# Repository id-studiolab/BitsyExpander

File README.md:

[![CC BY 4.0][cc-by-shield]][cc-by]

# Bitsy Expander

An expansion board adding support for the Grove solderless connector system, a WiFi radio, and LiPo battery charging circuitry to Adafruit ItsyBitsy Development Boards.

Compatible with all ItsyBitsy boards, the Bitsy Expander is available in two distinct flavors. The silkscreens on each flavor are specifically tailored to either the [ItsyBitsy M4 Express](https://www.adafruit.com/product/3800) or the [ItsyBitsy RP2040](https://www.adafruit.com/product/4888).

**Jump ahead:**

* [Bitsy Expander M4](#bitsy-expander-m4)
* [Bitsy Expander RP2040](#bitsy-expander-rp2040)
* [General Information](#general-information)
* [FAQ](#faq)
* [Version History](#version-history)

## Bitsy Expander M4

### Preview

### Features

* 12 Grove Headers
  - 5 Digital Headers with overlapping (shingled) pins: D2, D3, D4, D7, D13
  - 1 Digital Header with exclusive pins: SERIAL1
  - 3 Analog Headers with exclusive pins: A0, A2, A4
  - 3 I²C Headers
* ESP32-WROOM Co-Processor for WiFi and BLE
* 1 JST SH 4-pin connector for Qwiic and STEMMA QT components (I²C)
* 1 JST PH 2-pin connector for 3.7V LiPo Batteries (chargeable via ItsyBitsy's USB port)
* 1 Logic-shifted output (allows driving components requiring 5V logic while powered via USB)

> NOTE: In shingled pin headers, each header's second pin is shared with the first pin in the header above it. Therefore, using one disables the other. For instance, using pins D3 and D4 in the  D3-labeled header disallows the use of D4 in the D4-labeled header.

### Pinout Diagrams

Additional resources and pinout diagrams are available **[here](M4_info.md)**.

## Bitsy Expander RP2040

### Preview

### Features

* 12 Grove Headers
  - 5 Digital Headers with overlapping (shingled) pins: D2, D3, D4, D7, D13
  - 1 Digital Header with exclusive pins: UART0
  - 3 Analog Headers with exclusive pins: A0, A2, A3 (A2 and A3 contain digital pins for their second pins)
  - 3 I²C Headers
* ESP32-WROOM Co-Processor for WiFi and BLE
* 1 JST SH 4-pin connector for Qwiic and STEMMA QT components (I²C)
* 1 JST PH 2-pin connector for 3.7V LiPo Batteries (chargeable via ItsyBitsy's USB port)
* 1 Logic-shifted output (allows driving components requiring 5V logic while powered via USB)

> NOTE: In shingled pin headers, each header's second pin is shared with the first pin in the header above it. Therefore, using one disables the other. For instance, using pins D3 and D4 in the  D3-labeled header disallows the use of D4 in the D4-labeled header.

### Pinout Diagrams

Additional resources and pinout diagrams are available **[here](RP2040_info.md)**.

## General Information

### WiFi and BLE

The Bitsy Expander uses an ESP32 WROOM module to provide WiFi functionality to the microcontroller using [Adafruit's fork](https://github.com/adafruit/nina-fw) of the Arduino NINA-W102 firmware. In CircuitPython, this library also allows for the use of Bluetooth Low Energy (BLE).

To use the module with Circuitpython, use the [esp32spi](https://docs.circuitpython.org/projects/esp32spi/en/latest/) library. For Arduino, [Adafruit's forked WiFiNINA](https://github.com/adafruit/WiFiNINA/) library is required.

The ESP32 module is connected as follows:

| ESP32 Pin        | ItsyBitsy Pin |
| ---------------- | ------------- |
| Chip Select (CS) | D9            |
| Busy (BSY)       | D11           |
| Reset (RST)      | D12           |
| SPI Clock (SCK)  | SCK           |
| SPI MISO         | MISO          |
| SPI MOSI         | MOSI          |

### Solder Jumpers

The underside of the Bitsy Expander features a number of solder jumpers:

#### WIFI PIN:

These pins are used to connect the ItsyBitsy board to the ESP32 module on the Expander. If WiFi functionality is not needed but additional digital pins are required, these jumpers can be used to disable the WiFi module and make additional pins available in the double-row header on the upper side of the board. The traces between the middle and left pads must be severed before soldering a jumper in place between the middle and the right pads to do so.

#### ESP32 CONFIG:

These solder jumpers are normally open. If the ESP32 module requires a firmware update, these jumpers may be used to enable the ItsyBitsy to serve as a programming interface for the ESP32 module. Refer to [Adafruit's excellent tutorial](https://learn.adafruit.com/upgrading-esp32-firmware) on flashing firmware onto the ESP32.

#### BATTERY CHARGING:

The default battery charging current is 100mA. A faster, 500mA charging mode is available for batteries that support it. It can be enabled by closing the solder jumper.

## FAQ

#### How do I recognize which Bitsy Expander I have?

The easiest way to identify which Bitsy Expander flavor you own is checking the label on the back of the board. **RP2040** or **M4** stated on the label indicates the flavor of your Expander. Older M4 Expanders have an **empty label** (and are also recognizable by the lack of an I²C header at the top). 

#### How do I recognize which ItsyBitsy Development Board I am using?

The **ItsyBitsy M4 Express** features **one (RESET) button**. (So do most other ItsyBitsy Development boards, so always verify with the silkscreen.)
The **ItsyBitsy RP2040** features **two (BOOT, RESET) buttons**.

#### Will any ItsyBitsy-type microcontroller work with any Bitsy Expander?

In principle, yes. The silkscreen on either flavor is specifically designed for either the [ItsyBitsy M4 Express](https://www.adafruit.com/product/3800) or the [ItsyBitsy RP2040](https://www.adafruit.com/product/4888), respectively. Pinouts differ only slightly between ItsyBitsy Development boards, however. The M4 Expander, for instance, has also been used successfully with the [ItsyBitsy M0 Express](https://www.adafruit.com/product/3727) in the past. This repository includes a number of pinout diagrams for different use-cases.

## Version History

| Version | Comment                                                      | Known Issues                                                 | Flavors            |
| ------- | ------------------------------------------------------------ | ------------------------------------------------------------ | ------------------ |
| **1.0** | Initial version                                              | Using pin D13 to drive the ESP Chip Select (CS) causes interference between the microcontroller's internal LED and the pull-up resistor | M4 Express         |
| 1.1     | – Uses pin D9 instead of D13 to drive the ESP Chip Select to prevent interference  <br />– Adds a test point to the expander's underside for VBAT accessibility | Only two Grove headers provide direct access to Analog pins of used with RP2040 | M4 Express, RP2040 |
| **2.0** | – Adds a top-edge JST SH 4-pin connector for Qwiic and STEMMA QT compatibility  <br />– Repositions pin A3 for better RP2040 analog pin access<br />– Adds "NC" (not connected) labels to double-row header pins that are not normally broken out | Tilde (~) marks inaccurately represent freely configurable PWM pins on RP2040. *Note: all pins support PWM, subject to certain limitations.* | RP2040             |
| 2.1     | Silkscreen update to accurately depict a selection of freely configurable PWM pins on RP2040, preventing configuration conflicts among them |                                                              | RP2040             |
| **3.0** | – Reinstates original pin layout (identical to V1) for sequential analog pin placement on M4 Express <br />– Maintains JST SH-4 connector and VBAT test point inherited from previous versions |                                                              | M4 Express         |

This is the sibling of the [Nano Expander](https://github.com/id-studiolab/NanoExpander), a Grove expansion board for [Arduino Nano 33 IoT](https://store.arduino.cc/products/arduino-nano-33-iot).

This work is licensed under a
[Creative Commons Attribution 4.0 International License][cc-by].

[![CC BY 4.0][cc-by-image]][cc-by]

[cc-by]: http://creativecommons.org/licenses/by/4.0/
[cc-by-image]: https://i.creativecommons.org/l/by/4.0/88x31.png
[cc-by-shield]: https://img.shields.io/badge/License-CC%20BY%204.0-lightgrey.svg

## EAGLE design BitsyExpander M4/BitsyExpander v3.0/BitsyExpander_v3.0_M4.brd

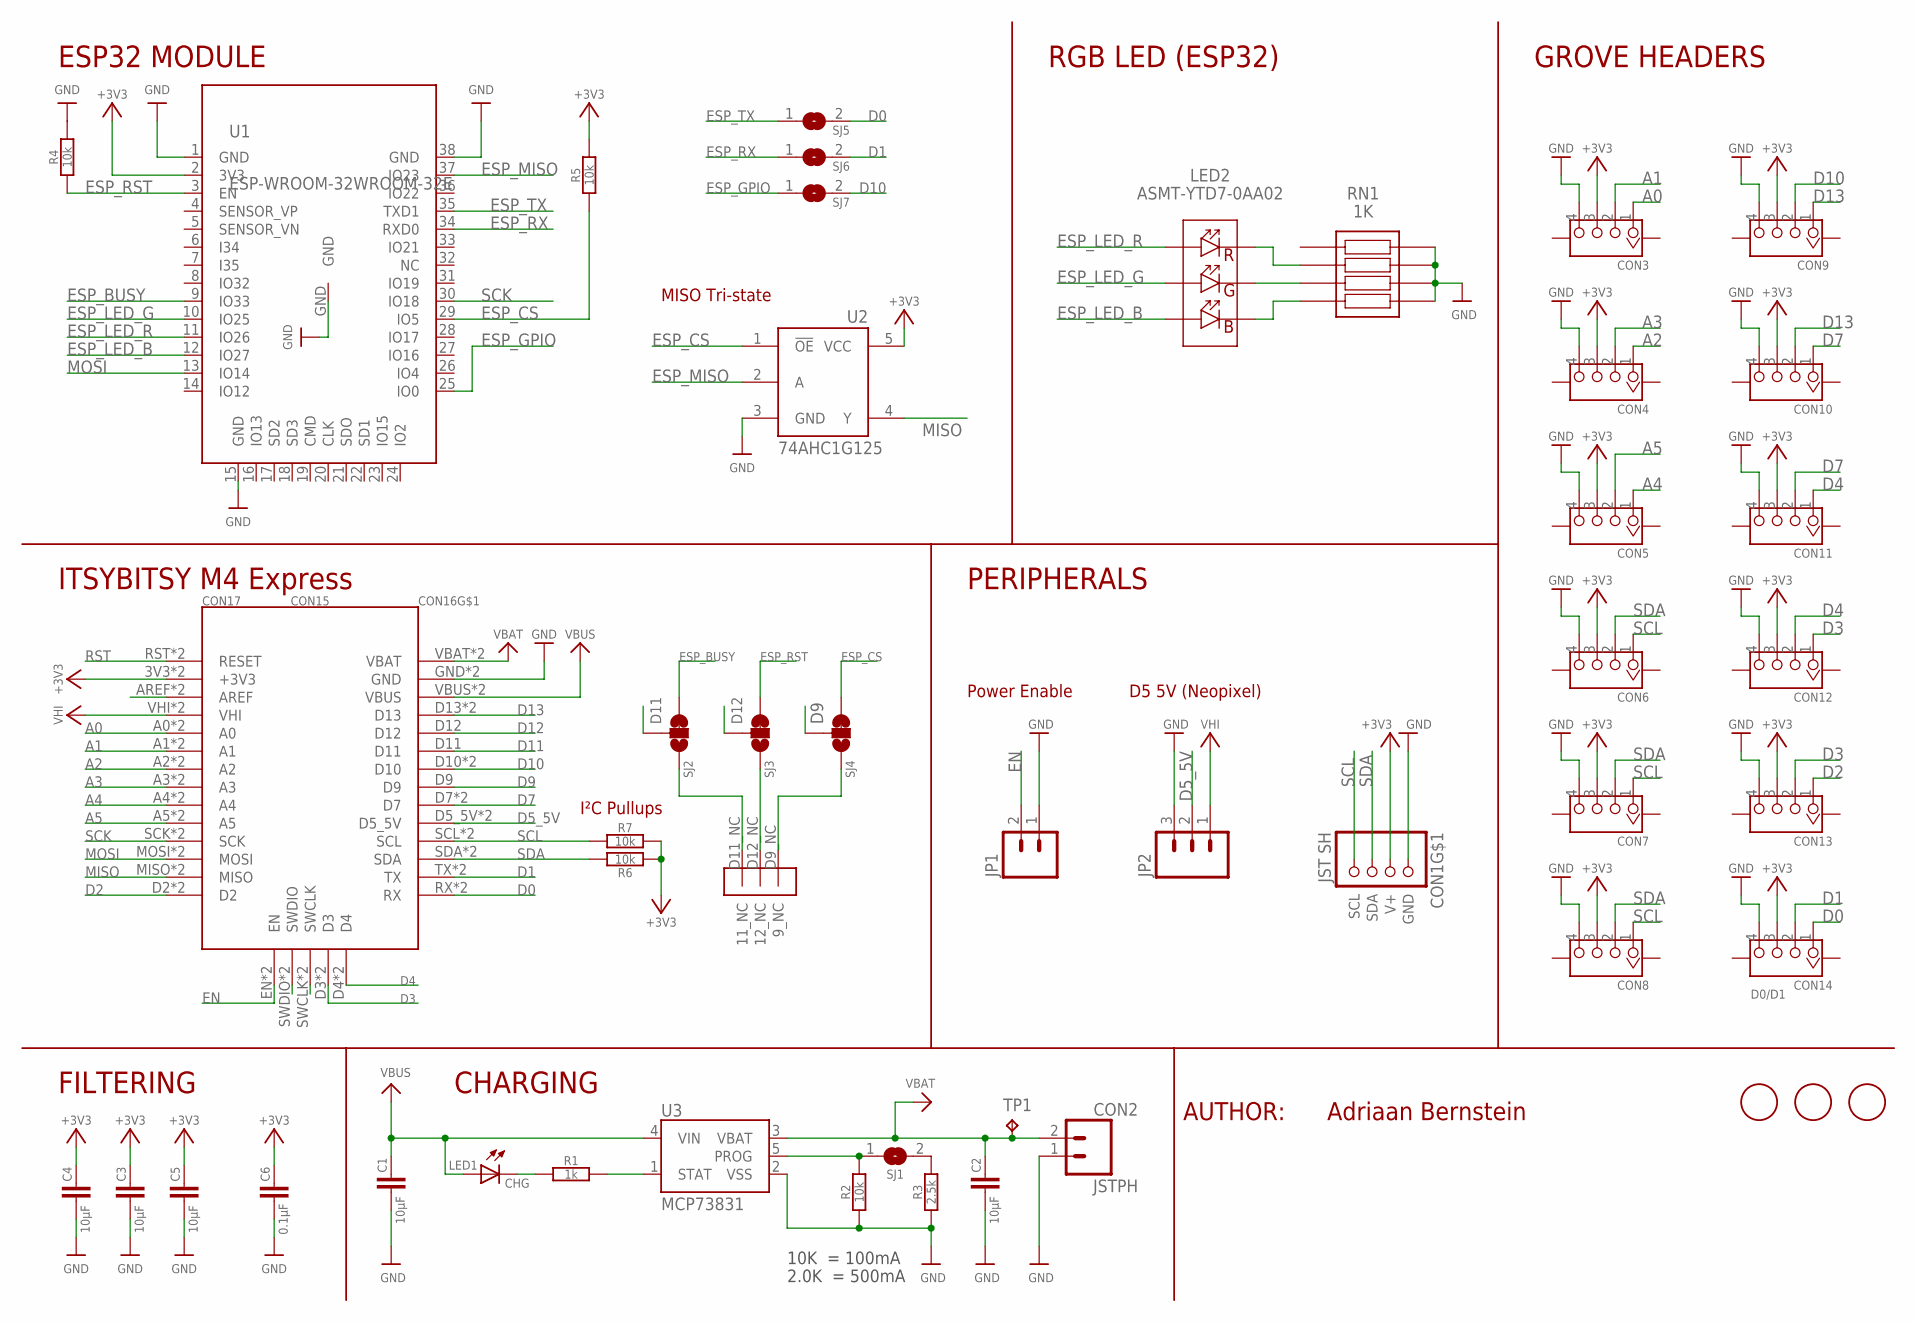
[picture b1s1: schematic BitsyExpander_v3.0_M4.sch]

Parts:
C1, C2, C3, C4, C5: 10µF; C0805
C6: 0.1µF; C0805
CON1: JST SH; JST_SH4
CON2: JSTPH; JST-2-SMD
CON3, CON4, CON5, CON6, CON7, CON8, CON9, CON10, CON11, CON12, CON13, CON14: H4P-SMD-2.0; HW4-PTH-2.0
CON15: ITSYBITSY_EDGE_DEBUG; ITSYBITSY_PTH_EDGE_DEBUG
CON16: ITSYBITSY_EDGE_GND; ITSYBITSY_SMD_EDGE_GND
CON17: ITSYBITSY_EDGE_PWR_M4EXPRESS; ITSYBITSY_SMD_EDGE_PWR_M4EXPRESS
FD1, FD2, FD3: FIDUCIAL; FIDUCIAL_1MM
JP1: M02PTH; 1X02
JP2: M03PTH; 1X03
LED1: CHG; CHIP-LED0603
LED2: ASMT-YTD7-0AA02; ASMTYTD70AA02
R1: 1k; R0603
R2, R4, R5, R6, R7: 10k; R0603
R3: 2.5k; R0603
RN1: 1K; CAY1647R0F4LF
SJ1, SJ5, SJ6, SJ7: SJ
SJ_D11: SJ2; SJ_2WAY_CLOSED
SJ_D12: SJ3; SJ_2WAY_CLOSED
SJ_D13: SJ4; SJ_2WAY_CLOSED
TP1: TPB1,27; B1,27
U1: ESP-WROOM-32WROOM-32E; ESP-WROOM-32E
U2: 74AHC1G125; SOT23-5L
U3: MCP73831; SOT23-5

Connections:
2.5K: R3.2, SJ1.2
10K: R2.2, SJ1.1, U3.5 (PROG)
+3V3: C3.1, C4.1, C5.1, C6.1, CON1.2 (V+), CON3.3, CON4.3, CON5.3, CON6.3, CON7.3, CON8.3, CON9.3, CON10.3, CON11.3, CON12.3, CON13.3, CON14.3, CON17.3V3 (+3V3), CON17.3V3_2 (+3V3), R5.2, R6.1, R7.1, U1.2 (3V3), U2.5 (VCC)
+5V: CON17.VHI, CON17.VHI_2 (VHI), JP2.1
A0: CON3.1, CON17.A0, CON17.A0_2 (A0)
A1: CON3.2, CON17.A1, CON17.A1_2 (A1)
A2: CON4.1, CON17.A2, CON17.A2_2 (A2)
A3: CON4.2, CON17.A3, CON17.A3_2 (A3)
A4: CON5.1, CON17.A4, CON17.A4_2 (A4)
A5: CON5.2, CON17.A5, CON17.A5_2 (A5)
AREF: CON17.AREF, CON17.AREF_2 (AREF)
CHG: LED1.C, R1.1
D0: CON14.1, CON15.RX, CON15.RX_2 (RX), SJ5.2
D1: CON14.2, CON16.TX, CON16.TX_2 (TX), SJ6.2
D2: CON13.1, CON15.D2, CON15.D2_2 (D2)
D3: CON12.1, CON13.2, CON15.D3, CON15.D3_2 (D3)
D4: CON11.1, CON12.2, CON15.D4, CON15.D4_2 (D4)
D5_5V: CON16.D5_5V, CON16.D5_5V_2 (D5_5V), JP2.2
D7: CON10.1, CON11.2, CON16.D7, CON16.D7_2 (D7)
D9: CON16.D9, SJ_D13.2
D9_NC: CON16.D9_NC (9_NC), SJ_D13.3
D10: CON9.2, CON16.D10, CON16.D10_2 (D10), SJ7.2
D11: CON16.D11, SJ_D11.2
D11_NC: CON16.D11_NC (11_NC), SJ_D11.3
D12: CON16.D12, SJ_D12.2
D12_NC: CON16.D12_NC (12_NC), SJ_D12.3
D13: CON9.1, CON10.2, CON16.D13, CON16.D13_2 (D13)
EN: CON15.EN, CON15.EN_2 (EN), JP1.2
ESP_BUSY: SJ_D11.1, U1.9 (IO33)
ESP_CS: R5.1, SJ_D13.1, U1.29 (IO5), U2.1 (!OE)
ESP_GPIO: SJ7.1, U1.25 (IO0)
ESP_LED_B: LED2.6 (A_BLUE), U1.12 (IO27)
ESP_LED_G: LED2.5 (A_GREEN), U1.10 (IO25)
ESP_LED_R: LED2.4 (A_RED), U1.11 (IO26)
ESP_MISO: U1.37 (IO23), U2.2 (A)
ESP_RST: R4.1, SJ_D12.1, U1.3 (EN)
ESP_RX: SJ6.1, U1.34 (RXD0)
ESP_TX: SJ5.1, U1.35 (TXD1)
GND: C1.2, C2.2, C3.2, C4.2, C5.2, C6.2, CON1.1 (GND), CON2.1, CON3.4, CON4.4, CON5.4, CON6.4, CON7.4, CON8.4, CON9.4, CON10.4, CON11.4, CON12.4, CON13.4, CON14.4, CON16.GND, CON16.GND_2 (GND), JP1.1, JP2.3, R2.1, R3.1, R4.2, RN1.5 (R4_2), RN1.6 (R3_2), RN1.7 (R2_2), RN1.8 (R1_2), U1.1 (GND), U1.15 (GND), U1.38 (GND), U1.GND, U2.3 (GND), U3.2 (VSS)
MISO: CON17.MISO, CON17.MISO_2 (MISO), U2.4 (Y)
MOSI: CON17.MOSI, CON17.MOSI_2 (MOSI), U1.13 (IO14)
unnamed: LED2.2 (K_GREEN), RN1.3 (R3_1)
unnamed: LED2.1 (K_BLUE), RN1.4 (R4_1)
unnamed: LED2.3 (K_RED), RN1.2 (R2_1)
unnamed: CON15.SWDIO, CON15.SWDIO_2 (SWDIO)
unnamed: CON15.SWCLK, CON15.SWCLK_2 (SWCLK)
RST: CON17.RST (RESET), CON17.RST_2 (RESET)
SCK: CON17.SCK, CON17.SCK_2 (SCK), U1.30 (IO18)
SCL: CON1.4 (SCL), CON6.1, CON7.1, CON8.1, CON16.SCL, CON16.SCL_2 (SCL), R7.2
SDA: CON1.3 (SDA), CON6.2, CON7.2, CON8.2, CON16.SDA, CON16.SDA_2 (SDA), R6.2
STAT: R1.2, U3.1 (STAT)
VBAT: C2.1, CON2.2, CON16.VBAT, CON16.VBAT_2 (VBAT), TP1.TP, U3.3 (VBAT)
VBUS: C1.1, CON16.VBUS, CON16.VBUS_2 (VBUS), LED1.A, U3.4 (VIN)

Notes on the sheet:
10K = 100mA
2.0K = 500mA
D0/D1
FILTERING
CHARGING
PERIPHERALS
GROVE HEADERS
ITSYBITSY M4 Express
ESP32 MODULE
RGB LED (ESP32)
MISO Tri-state
Power Enable
D5 5V (Neopixel)
I²C Pullups
AUTHOR:
Adriaan Bernstein

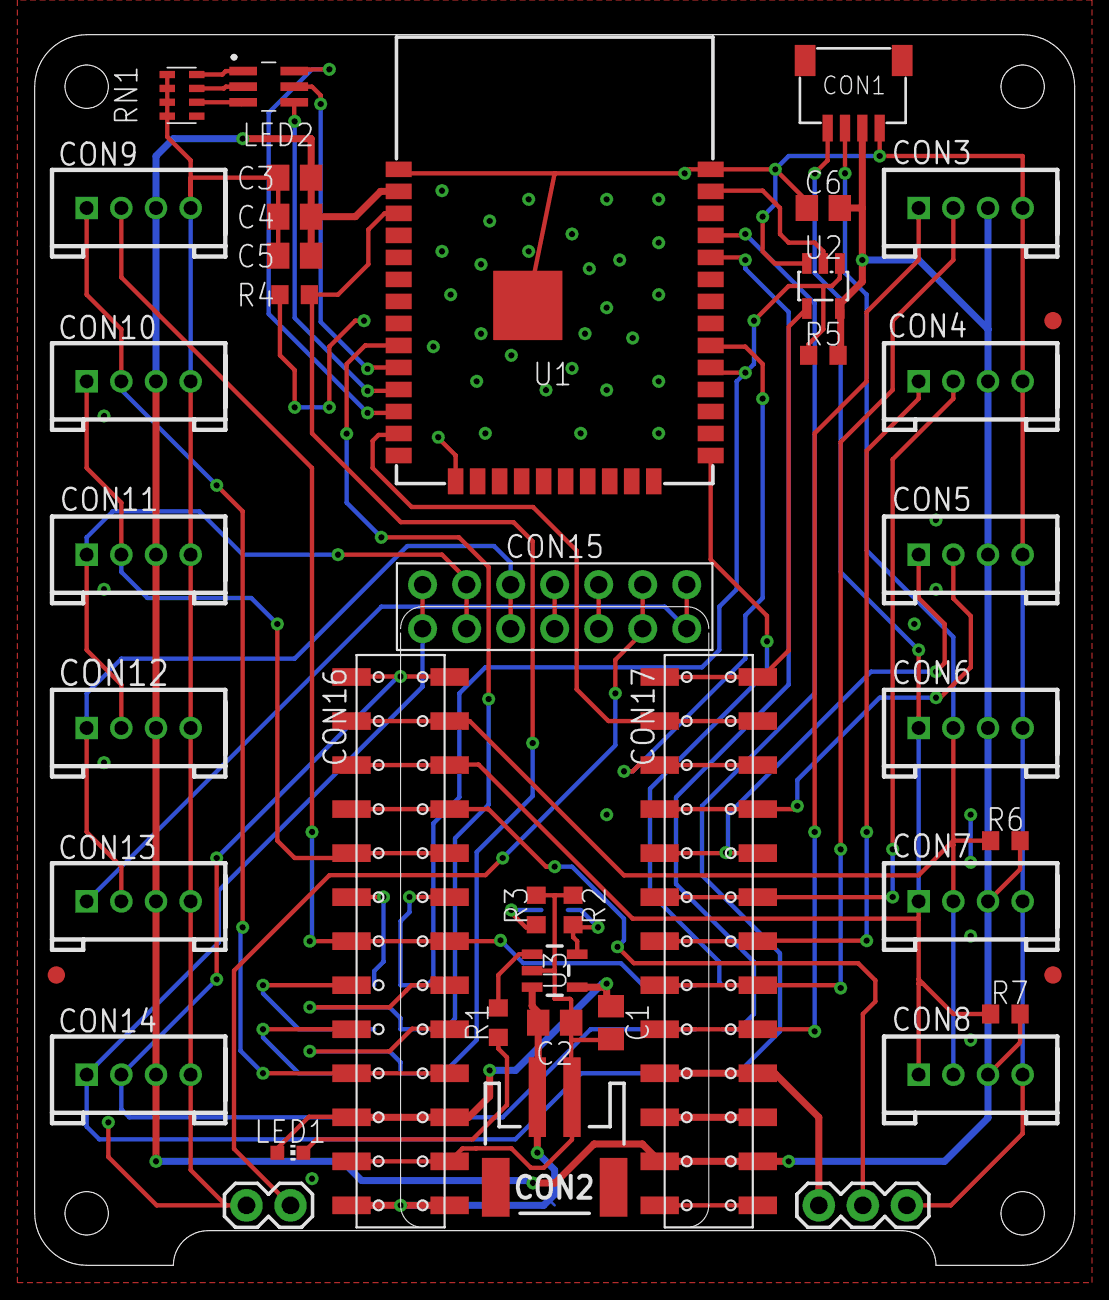
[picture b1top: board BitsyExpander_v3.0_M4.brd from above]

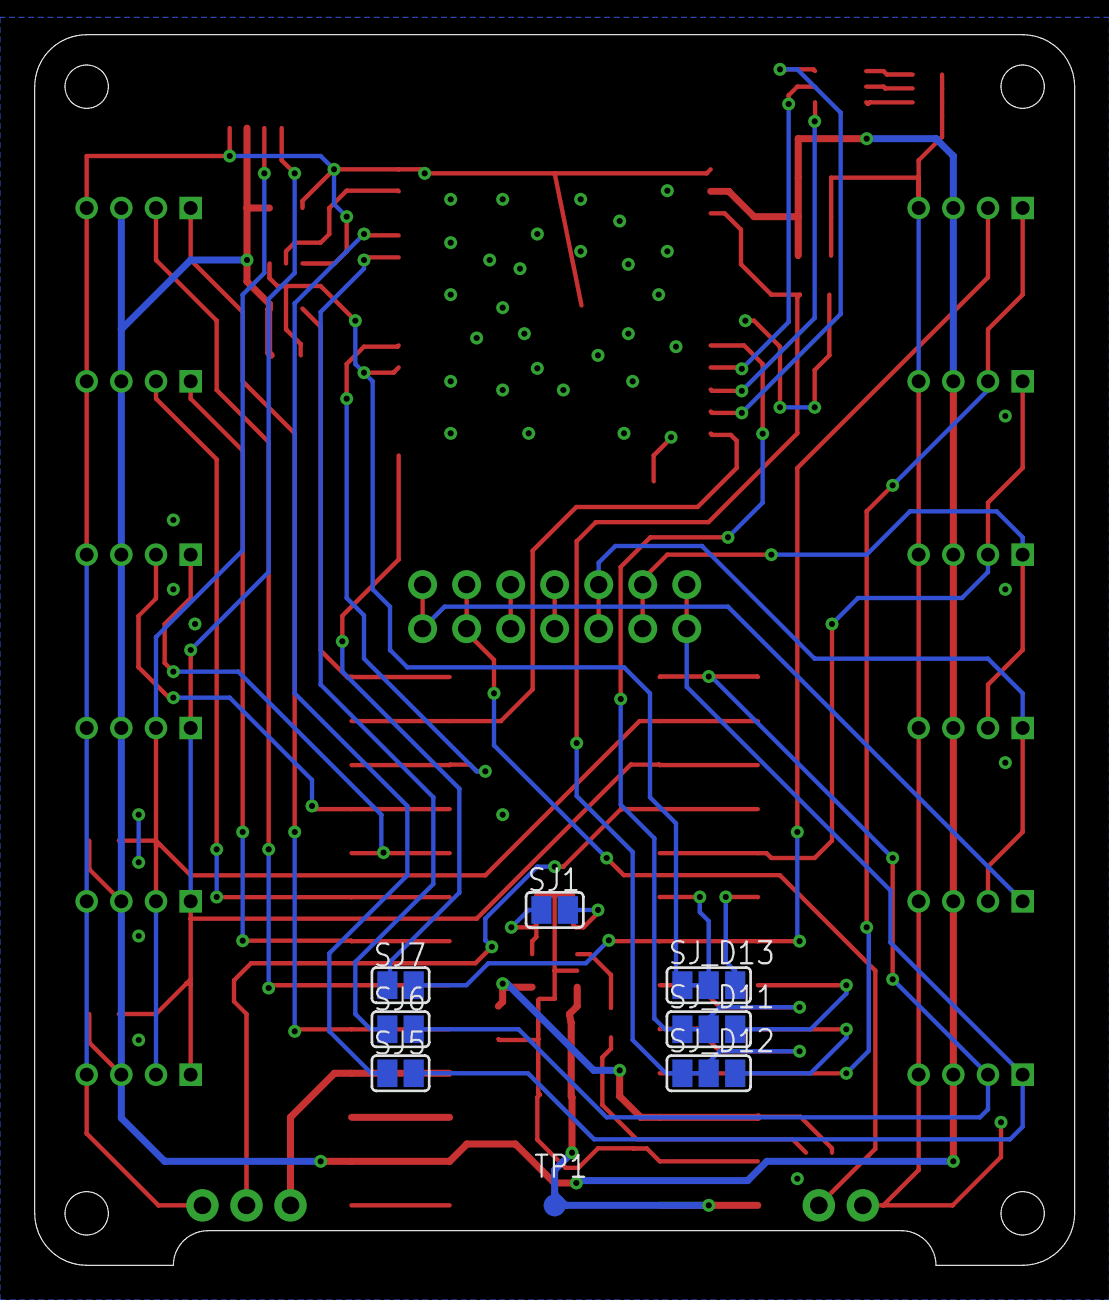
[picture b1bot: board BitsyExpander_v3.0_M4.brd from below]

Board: 2 copper layers, 60.0 x 71.0 mm, 49 parts (8 on the bottom side), 53 nets.

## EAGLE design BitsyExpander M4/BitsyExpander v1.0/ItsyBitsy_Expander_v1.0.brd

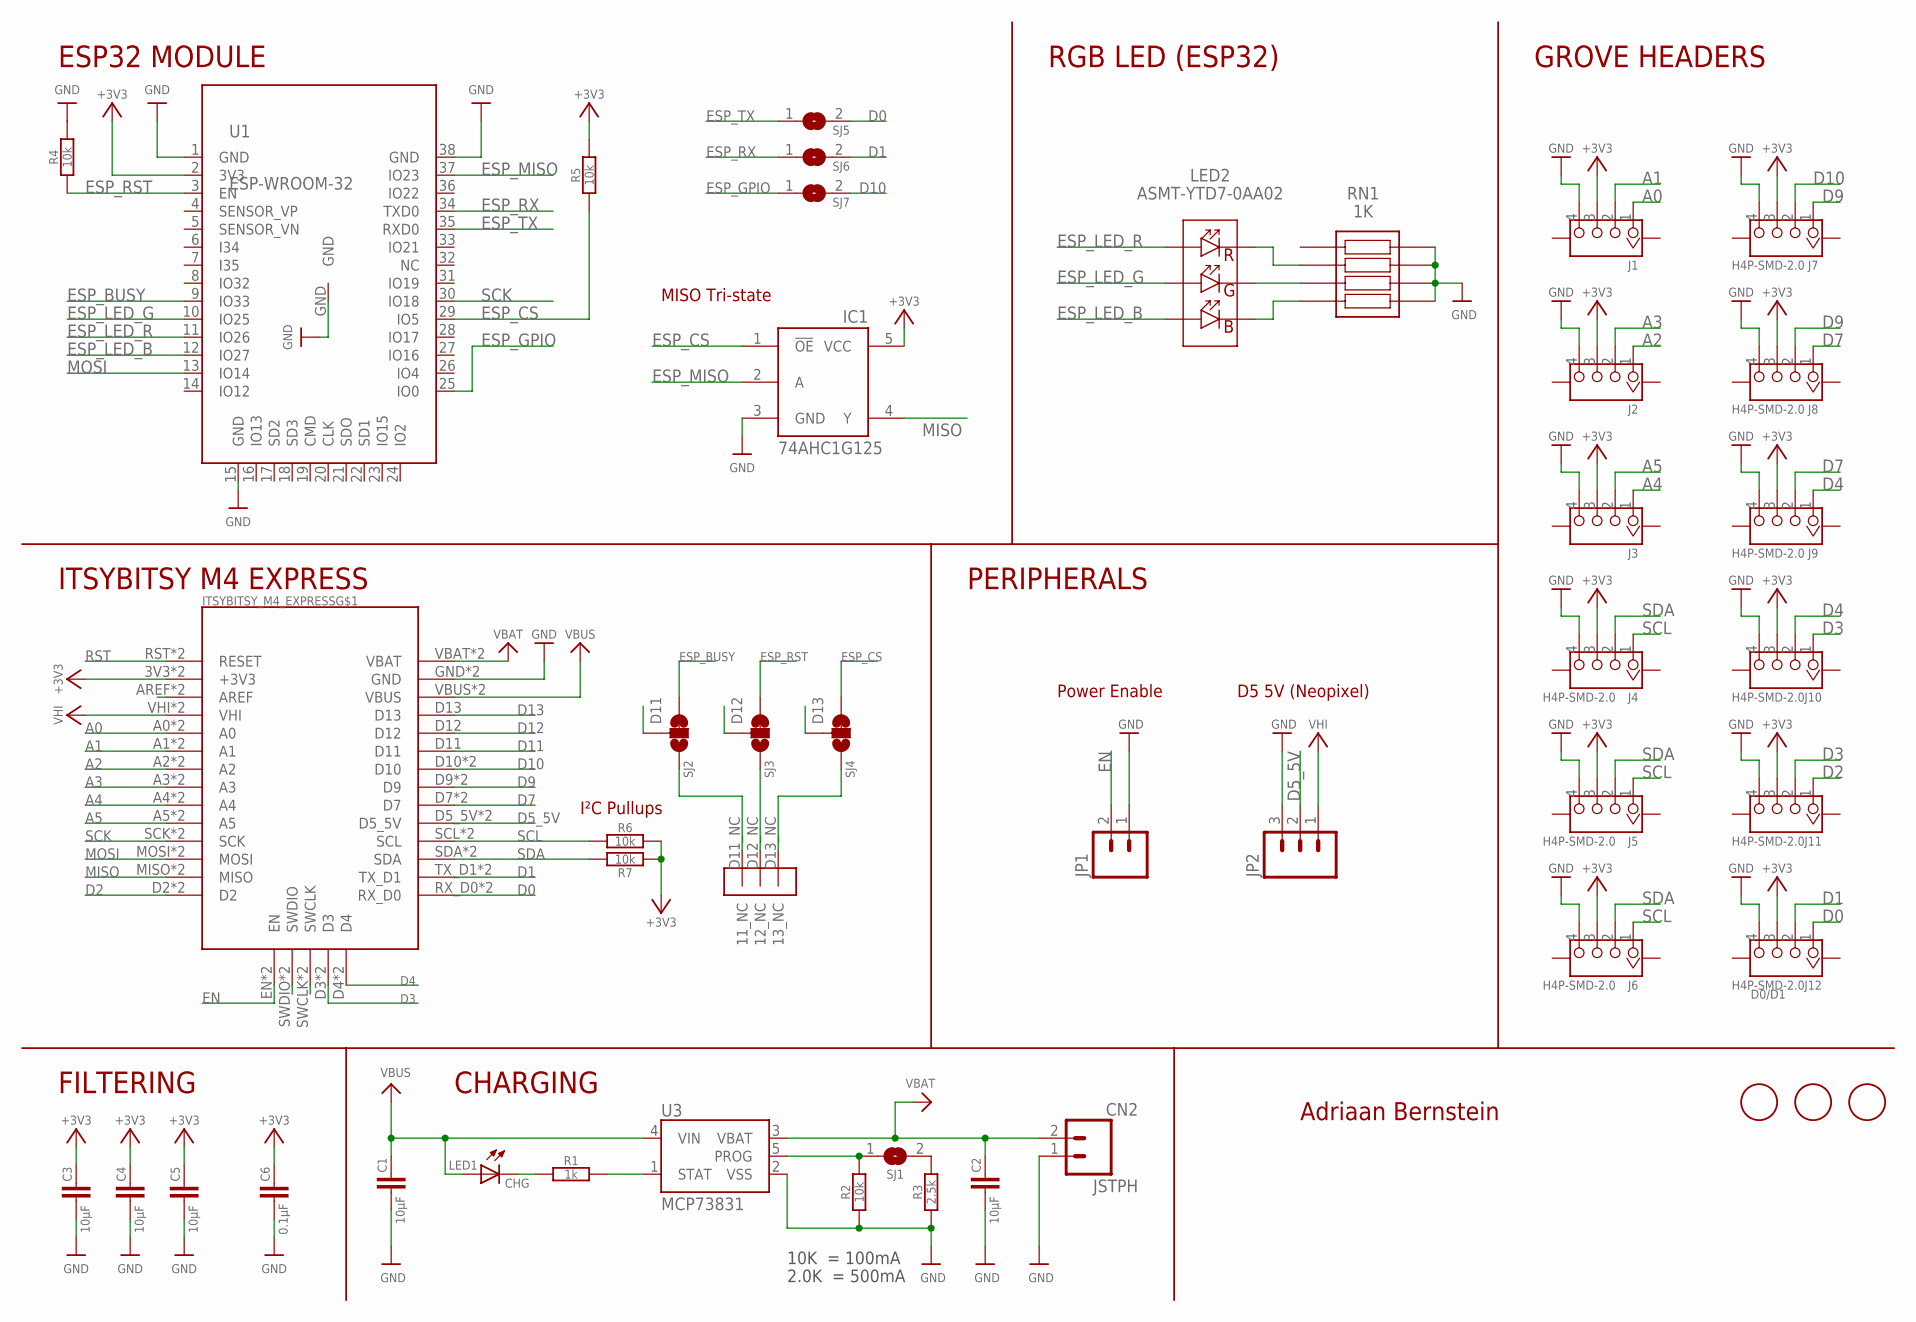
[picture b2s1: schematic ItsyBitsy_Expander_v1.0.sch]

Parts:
C1, C2, C3, C4, C5: 10µF; C0805
C6: 0.1µF; C0603
CN2: JSTPH; JST-2-SMD
IC1: 74AHC1G125; SOT23-5L
ITSYBITSY_M4_EXPRESS: ITSYBITSY_M4_NC; ITSYBITSY_M4_MIXED_DOUBLEHEADERS_ALL_NC
J1, J2, J3, J4, J5, J6, J7, J8, J9, J10, J11, J12: H4P-SMD-2.0; HW4-SMD-2.0
JP1: M02PTH; 1X02
JP2: M03PTH; 1X03
LED1: CHG; CHIP-LED0603
LED2: ASMT-YTD7-0AA02; ASMTYTD70AA02
R1: 1k; R0603
R2, R4, R5, R6, R7: 10k; R0603
R3: 2.5k; R0603
RN1: 1K; CAY1647R0F4LF
SJ1, SJ5, SJ6, SJ7: SJ
SJ_D11: SJ2; SJ_2WAY_CLOSED
SJ_D12: SJ3; SJ_2WAY_CLOSED
SJ_D13: SJ4; SJ_2WAY_CLOSED
U1: ESP-WROOM-32
U3: MCP73831; SOT23-5
U$23, U$35, U$36: FIDUCIAL; FIDUCIAL_1MM

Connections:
2.5K: R3.2, SJ1.2
10K: R2.2, SJ1.1, U3.5 (PROG)
+3V3: C3.1, C4.1, C5.1, C6.1, IC1.5 (VCC), ITSYBITSY_M4_EXPRESS.3V3 (+3V3), ITSYBITSY_M4_EXPRESS.3V3_2 (+3V3), J1.3, J2.3, J3.3, J4.3, J5.3, J6.3, J7.3, J8.3, J9.3, J10.3, J11.3, J12.3, R5.2, R6.1, R7.1, U1.2 (3V3)
+5V: ITSYBITSY_M4_EXPRESS.VHI, ITSYBITSY_M4_EXPRESS.VHI_2 (VHI), JP2.1
A0: ITSYBITSY_M4_EXPRESS.A0, ITSYBITSY_M4_EXPRESS.A0_2 (A0), J1.1
A1: ITSYBITSY_M4_EXPRESS.A1, ITSYBITSY_M4_EXPRESS.A1_2 (A1), J1.2
A2: ITSYBITSY_M4_EXPRESS.A2, ITSYBITSY_M4_EXPRESS.A2_2 (A2), J2.1
A3: ITSYBITSY_M4_EXPRESS.A3, ITSYBITSY_M4_EXPRESS.A3_3 (A3), J2.2
A4: ITSYBITSY_M4_EXPRESS.A4, ITSYBITSY_M4_EXPRESS.A4_2 (A4), J3.1
A5: ITSYBITSY_M4_EXPRESS.A5, ITSYBITSY_M4_EXPRESS.A5_2 (A5), J3.2
CHG: LED1.C, R1.1
D0: ITSYBITSY_M4_EXPRESS.RX_D0, ITSYBITSY_M4_EXPRESS.RX_D0_2 (RX_D0), J12.1, SJ5.2
D1: ITSYBITSY_M4_EXPRESS.TX_D1, ITSYBITSY_M4_EXPRESS.TX_D1_2 (TX_D1), J12.2, SJ6.2
D2: ITSYBITSY_M4_EXPRESS.D2, ITSYBITSY_M4_EXPRESS.D2_2 (D2), J11.1
D3: ITSYBITSY_M4_EXPRESS.D3, ITSYBITSY_M4_EXPRESS.D3_2 (D3), J10.1, J11.2
D4: ITSYBITSY_M4_EXPRESS.D4, ITSYBITSY_M4_EXPRESS.D4_2 (D4), J9.1, J10.2
D5_5V: ITSYBITSY_M4_EXPRESS.D5_5V, ITSYBITSY_M4_EXPRESS.D5_5V_2 (D5_5V), JP2.2
D7: ITSYBITSY_M4_EXPRESS.D7, ITSYBITSY_M4_EXPRESS.D7_2 (D7), J8.1, J9.2
D9: ITSYBITSY_M4_EXPRESS.D9, ITSYBITSY_M4_EXPRESS.D9_2 (D9), J7.1, J8.2
D10: ITSYBITSY_M4_EXPRESS.D10, ITSYBITSY_M4_EXPRESS.D10_2 (D10), J7.2, SJ7.2
D11: ITSYBITSY_M4_EXPRESS.D11, SJ_D11.2
D11_NC: ITSYBITSY_M4_EXPRESS.D11_NC (11_NC), SJ_D11.3
D12: ITSYBITSY_M4_EXPRESS.D12, SJ_D12.2
D12_NC: ITSYBITSY_M4_EXPRESS.D12_NC (12_NC), SJ_D12.3
D13: ITSYBITSY_M4_EXPRESS.D13, SJ_D13.2
D13_NC: ITSYBITSY_M4_EXPRESS.D13_NC (13_NC), SJ_D13.3
EN: ITSYBITSY_M4_EXPRESS.EN, ITSYBITSY_M4_EXPRESS.EN_2 (EN), JP1.2
ESP_BUSY: SJ_D11.1, U1.9 (IO33)
ESP_CS: IC1.1 (!OE), R5.1, SJ_D13.1, U1.29 (IO5)
ESP_GPIO: SJ7.1, U1.25 (IO0)
ESP_LED_B: LED2.6 (A_BLUE), U1.12 (IO27)
ESP_LED_G: LED2.5 (A_GREEN), U1.10 (IO25)
ESP_LED_R: LED2.4 (A_RED), U1.11 (IO26)
ESP_MISO: IC1.2 (A), U1.37 (IO23)
ESP_RST: R4.1, SJ_D12.1, U1.3 (EN)
ESP_RX: SJ6.1, U1.34 (TXD0)
ESP_TX: SJ5.1, U1.35 (RXD0)
GND: C1.2, C2.2, C3.2, C4.2, C5.2, C6.2, CN2.1, IC1.3 (GND), ITSYBITSY_M4_EXPRESS.GND, ITSYBITSY_M4_EXPRESS.GND_2 (GND), J1.4, J2.4, J3.4, J4.4, J5.4, J6.4, J7.4, J8.4, J9.4, J10.4, J11.4, J12.4, JP1.1, JP2.3, R2.1, R3.1, R4.2, RN1.5 (R4_2), RN1.6 (R3_2), RN1.7 (R2_2), RN1.8 (R1_2), U1.1 (GND), U1.15 (GND), U1.38 (GND), U1.GND, U3.2 (VSS)
MISO: IC1.4 (Y), ITSYBITSY_M4_EXPRESS.MISO, ITSYBITSY_M4_EXPRESS.MISO_2 (MISO)
MOSI: ITSYBITSY_M4_EXPRESS.MOSI, ITSYBITSY_M4_EXPRESS.MOSI_2 (MOSI), U1.13 (IO14)
unnamed: LED2.2 (K_GREEN), RN1.3 (R3_1)
unnamed: LED2.1 (K_BLUE), RN1.4 (R4_1)
unnamed: LED2.3 (K_RED), RN1.2 (R2_1)
unnamed: ITSYBITSY_M4_EXPRESS.AREF, ITSYBITSY_M4_EXPRESS.AREF_2 (AREF)
unnamed: ITSYBITSY_M4_EXPRESS.SWDIO, ITSYBITSY_M4_EXPRESS.SWDIO_2 (SWDIO)
unnamed: ITSYBITSY_M4_EXPRESS.SWCLK, ITSYBITSY_M4_EXPRESS.SWCLK_2 (SWCLK)
RST: ITSYBITSY_M4_EXPRESS.RST (RESET), ITSYBITSY_M4_EXPRESS.RST_2 (RESET)
SCK: ITSYBITSY_M4_EXPRESS.SCK, ITSYBITSY_M4_EXPRESS.SCK_2 (SCK), U1.30 (IO18)
SCL: ITSYBITSY_M4_EXPRESS.SCL, ITSYBITSY_M4_EXPRESS.SCL_2 (SCL), J4.1, J5.1, J6.1, R6.2
SDA: ITSYBITSY_M4_EXPRESS.SDA, ITSYBITSY_M4_EXPRESS.SDA_2 (SDA), J4.2, J5.2, J6.2, R7.2
STAT: R1.2, U3.1 (STAT)
VBAT: C2.1, CN2.2, ITSYBITSY_M4_EXPRESS.VBAT, ITSYBITSY_M4_EXPRESS.VBAT_2 (VBAT), U3.3 (VBAT)
VBUS: C1.1, ITSYBITSY_M4_EXPRESS.VBUS, ITSYBITSY_M4_EXPRESS.VBUS_2 (VBUS), LED1.A, U3.4 (VIN)

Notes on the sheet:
10K = 100mA
2.0K = 500mA
D0/D1
FILTERING
CHARGING
PERIPHERALS
GROVE HEADERS
ITSYBITSY M4 EXPRESS
ESP32 MODULE
RGB LED (ESP32)
MISO Tri-state
Power Enable
D5 5V (Neopixel)
Adriaan Bernstein
I²C Pullups

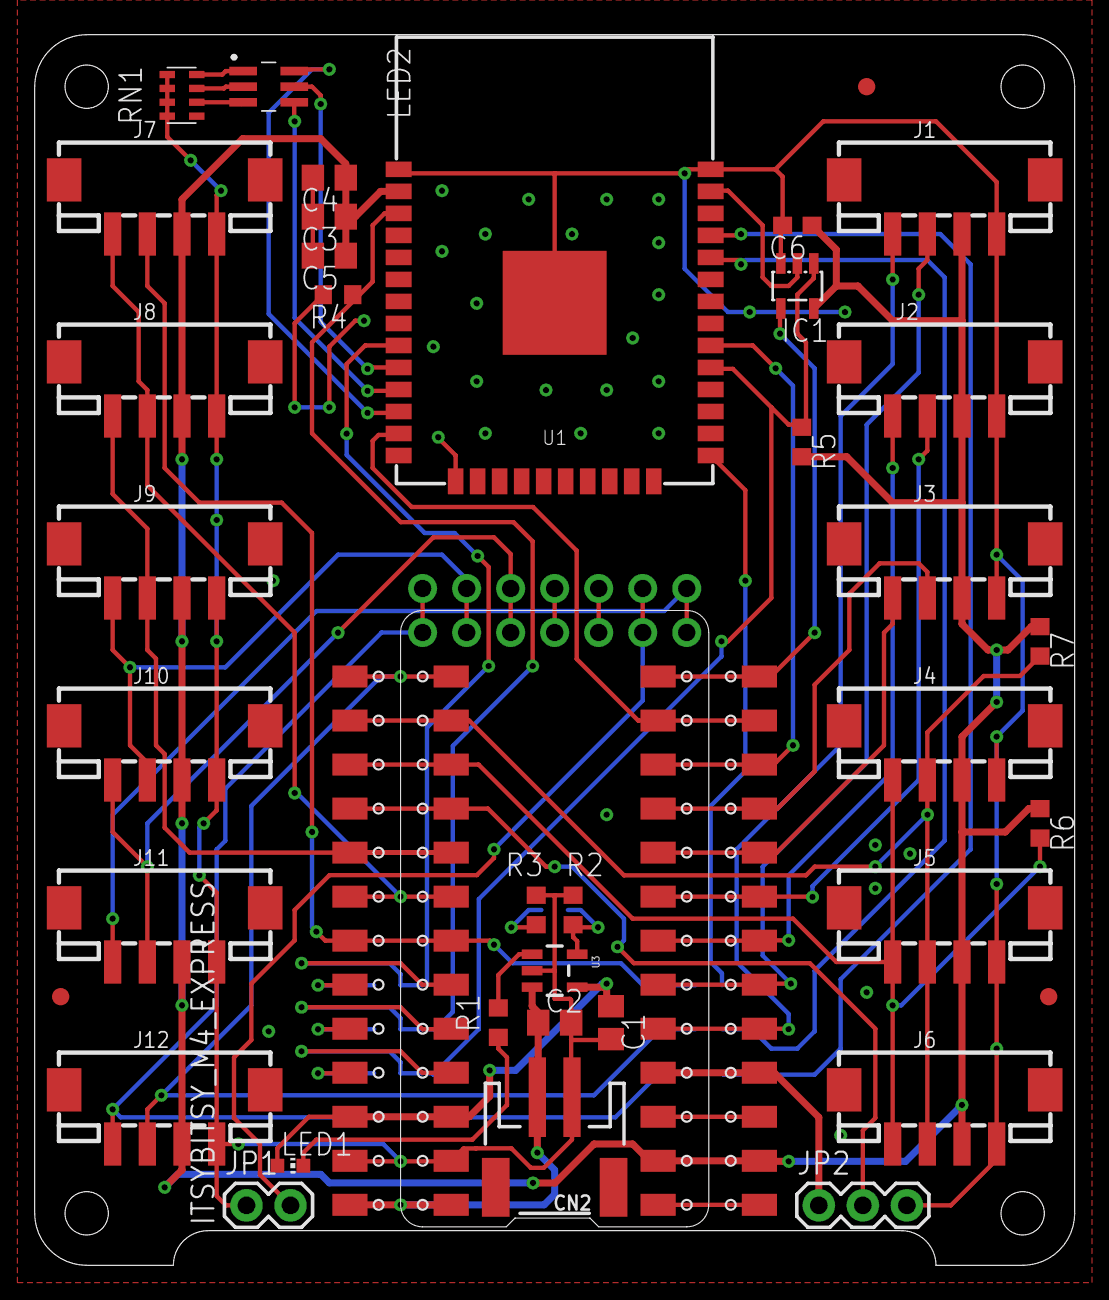
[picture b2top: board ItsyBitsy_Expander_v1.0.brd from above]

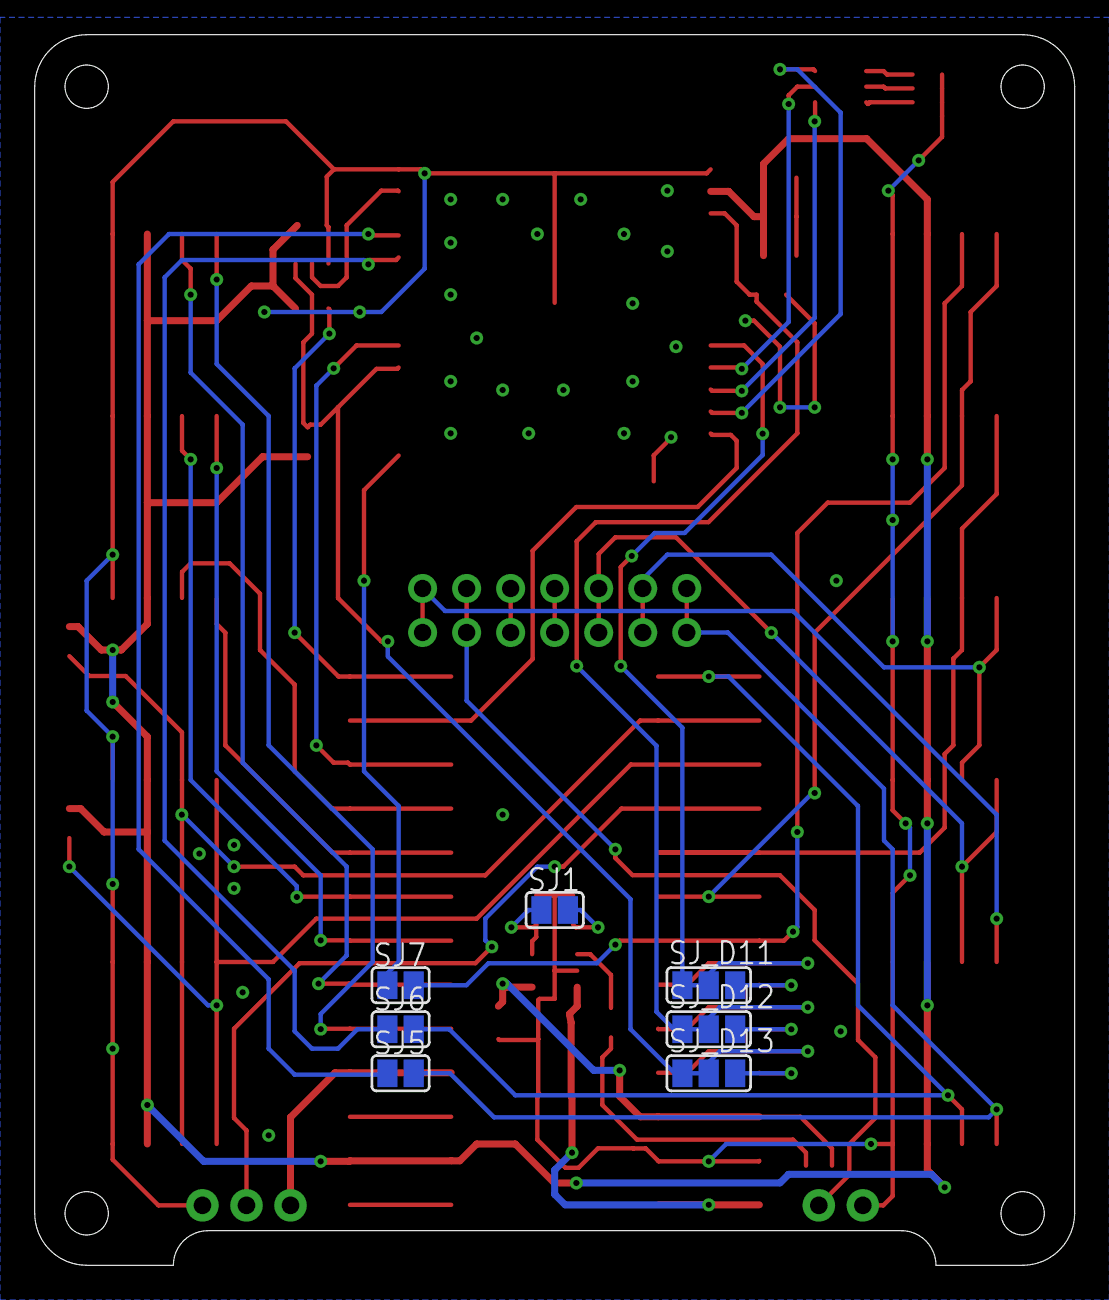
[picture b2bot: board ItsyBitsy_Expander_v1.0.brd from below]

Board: 2 copper layers, 60.0 x 71.0 mm, 45 parts (7 on the bottom side), 53 nets.

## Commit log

2020-11-16 V1.0 eagle files and assets
    Eagle files and assets
2020-11-16 Update README.md
    Add preview images
2020-11-25 Fix bug in ESP32 footprint
    Flip RX and TX pads
2020-12-02 Fix I²C footprint
2020-12-02 Upload V1.1
    * Use through-hole headers
    * Change CS pin for ESP32 coprocessor
    * Fix bugs in previous version (Serial breakout pads for ESP32, I²C header pinout)
2020-12-02 Update readme, file cleanup
2021-11-08 Create LICENSE
    Add license
2021-11-08 Add ENIG PCB Previews
    Add ENIG PCB Previews for consistency
2021-11-08 Update README.md
    Update PCB Preview for consistency
2021-12-29 Create RP2040_info.md
    Add documentation for ItsyBitsy RP2040
2023-06-14 Restructuring and Cleanup
2023-06-14 Version 3.0
2023-06-19 Version 3.0 Assets and updated Gerber fileswith custom silkscreen
2023-06-22 Add rev2.1, fixes to RP2040 specific silkscreen
2023-06-23 Update README; cleanup
2023-06-25 Include Pinout Diagrams
2023-06-25 Fix pinout diagram file format
2023-06-25 Add M4 pinout overview
2023-06-25 Link fix
2023-07-06 minor changes
2024-06-13 change to hardware license
